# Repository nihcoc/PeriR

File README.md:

# PeriR
> Under Development!

---

## Abstract

A custom Software Defined Radio (SDR) HAT built around the Xilinx Artix-7 XC7A50T FPGA and Analog Devices AD9364 RF transceiver.
This project is inspired by the [FreeSRP](http://electronics.kitchen/misc/freesrp/) open-source SDR by Lukas Lao Beyer and design references from the  <a href="https://wiki.analog.com/resources/eval/user-guides/ad-fmcomms4-ebz">FMCOMMS4</a>.

The goal is a powerful, Linux-capable SDR transceiver with a compact form factor and eventually, a handheld device like the HackRF Portapack.

---

## Key Specifications

| Feature | Detail |
|---|---|
| **SoM** | Compute Module 4 |
| **FPGA** | Xilinx Artix-7 XC7A50T FPGA |
| **RF Transceiver** | Analog Devices AD9364 |
| **Frequency Range** | 70 MHz – 6.0 GHz |
| **Bandwidth** | 200 kHz – 56 MHz |
| **Interfaces** | PCIe 2.0 x1, USB2.0 |
---

## Hardware Design

Read my <a href="https://github.com/nihcoc/PeriR/blob/main/perir-journal.md">Hardware Journal and 120 Hours of footage of my entire design process</a> here!

### RF
- **Balun:** TCM1-63AX+ wideband RF transformer (10MHz to 6GHz)
- **Clock:** 40 MHz TCXO
- **Power:** ADP1754ACPZ-1.3-R7 (Recommended by AD)
- **TX Power Amp:** PGA-102 (dedicated clean 3.3V supply)
- **Trace:** Output traces are 50Ω controlled for the JLC06161H-3313A stack-up, Co-planar and no solder mask

### Power Architecture

| Rail | IC | Current | 
|---|---|---|
| 1.0V | TPS62130A | 3A | 
| 1.8V | TPS62130A | 3A | 
| 3.3V | TPS62130A | 3A | 
| 2.5V | TPS62130A | 3A | 
| 1.2V | TPS62130A | 3A | 
| 1.3V | ADP1754ACPZ-1.3-R7 | 3A |
| 5V | External connector | ~ 8A  |

> Sequencing is managed using EN (Enable) and PG (Power Good) pins chained between power ICs. See Pg8 on ([DS181](https://docs.amd.com/v/u/en-US/ds181_Artix_7_Data_Sheet))

### Interfaces
**CM4 INTERFACES**
| CM4 Interface | Notes |
|---|---|
| **HDMI** | Length matched, 100Ω  Differential|
| **USB** | Length matched, 100Ω  Differential|
| **DSI** | Length matched, 100Ω  Differential |
| **SD Card** |  Length matched, 50Ω |
| **PCIe 2.0 x1** | ±1ps Length matched , 90Ω Differential (See ([Pg7 2.3](https://pip-assets.raspberrypi.com/categories/634-raspberry-pi-compute-module-4/documents/RP-008168-DS-4-cm4-datasheet.pdf)) ) |
| **DEBUG LEDS** | Blue leds for debug/status |

> Impedance controlled according to the JLC06161H-3313A stack-up using the [JLCPCB impedence calculator](https://jlcpcb.com/pcb-impedance-calculator)

**FPGA INTERFACES**
| FPGA Interface | Notes |
|---|---|
| **USB 2.0** | Routed for the asynchronous 245 FIFO mode on FT2232HL |
| **PCIe 2.0 x1** | GTP transceivers are only supported on a few Artix-7 chips such as the CSG-325 |
| **JTAG** | Bank_0 |
| **Transceiver Digital Interface** | Routing configured for the DUAL PORT FULL DUPLEX MODE using the LVDS signaling standard. LVDS mode is supported on the XC7A50T-CSG325 but only when VCCO_x is supplied with 2.5V|
| **DEBUG LEDS** | Blue leds for debug/status |

> Impedance for the layer 3 LVDS signals is not 100Ω because I mistakenly used the JLC06161H-3313E stackup to calculate the impedance for this layer. It's not ideal, but the traces are only around 3 cm long, so the impact of the mismatch should be relatively small. I can validate the interface at a lower data rate and use diagnostics and timing analysis to check the signal margin. I'll fix the impedance mismatch properly in V2.

---

###  Key Datasheets

| Part | Source |
|---|---|
| **XC7A50T** | [UG470 CONFIG/FLASH](https://docs.amd.com/v/u/en-US/ug470_7Series_Config) |
| **XC7A50T** | [DS181 POWER](https://docs.amd.com/v/u/en-US/ds181_Artix_7_Data_Sheet) |
| **XC7A50T** | [UG483 LAYOUT/CAPS](https://docs.amd.com/v/u/en-US/ug483_7Series_PCB) |
| **XC7A50T** | [UG482 GTP(PCIe)](https://docs.amd.com/v/u/en-US/ug482_7Series_GTP_Transceivers) |
| **XC7A50T** | [UG472 CLOCKING ](https://docs.amd.com/v/u/en-US/ug472_7Series_Clocking) |
| **AD9364** | [UG673 Main Reference](https://www.analog.com/media/en/technical-documentation/data-sheets/AD9364.pdf) |
| **AD9364** | [Overview](https://www.scribd.com/document/271013063/AD9364-Reference-Manual-UG-673) |
| **FT2232H** | [Main Reference](https://ftdichip.com/wp-content/uploads/2024/09/DS_FT2232H.pdf) |
| **Compute Module 4** | [Main Reference](https://pip-assets.raspberrypi.com/categories/634-raspberry-pi-compute-module-4/documents/RP-008168-DS-4-cm4-datasheet.pdf)|
| **TPS62130** | [Main Reference](https://www.ti.com/lit/gpn/TPS62130A)|
| **ADP1754ACPZ-1.3-R7** | [Main Reference](https://www.analog.com/media/en/technical-documentation/data-sheets/ADP1754_1755.pdf)|
| **NCP700BSN33T1G** | [Main Reference](https://www.onsemi.com/pdf/datasheet/ncp700b-d.pdf)|
| **ADM7160AUJZ-1.8-R7** | [Main Reference](https://www.analog.com/media/en/technical-documentation/data-sheets/ADM7160.pdf)|
| **TCM1-63AX+** | [Main Reference](https://www.minicircuits.com/pdfs/TCM1-63AX+.pdf)|
| **PGA-102+** | [Main Reference](https://www.minicircuits.com/pdfs/PGA-102+.pdf)|

---

## Software

CM4 - FPGA - AD9364 software/digital design interface is in development.

**General Software**

- **OS:** [Kuiper Linux](https://wiki.analog.com/resources/tools-software/linux-software/kuiper-linux) by Analog Devices
- **Reference HDL:** ([https://github.com/analogdevicesinc/hdl/blob/main/library/axi_ad9361/axi_ad9361.v](https://github.com/analogdevicesinc/hdl/blob/main/library/axi_ad9361/axi_ad9361.v))

---

## Layers

*Layer 1(Top)*

*Layer 2(GND)*

*Layer 3*

*Layer 4(Power)*
> IDK how I didn't notice but my power planes look hideous and probably subpar with those sharp edges and uneven clearances. Gotta fix this in V2.

*Layer 5(GND/LOW Speed Signals)*

*Layer 6(Bottom)*

---

## Bill of Materials

 Total = ~$485(excl. shipping)

| # | LCSC# | MPN | Manufacturer | Package | Board Ref | Description | Qty | MOQ | Unit Price ($) | Ext. Price ($) | Product Link |
|---|-------|-----|--------------|---------|-----------|-------------|-----|-----|---------------|----------------|--------------|
| 1 | C444946 | AD9364BBCZ | ADI | BGA-144 | U4 | -122dBm 70MHz~6GHz 1.2V~3.3V BGA-144 RF Transceiver ICs RoHS | 1 | 1 | 96.5166 | 96.52 | [Link](https://www.lcsc.com/product-detail/C444946.html) |
| 2 | C5199907 | SMA-J-P-H-ST-EM1 | Samtec | SMD | J12, J13, J14 | Connector Receptacle SMA 50Ω | 3 | 1 | 4.8959 | 14.69 | [Link](https://www.lcsc.com/product-detail/C5199907.html) |
| 3 | C337502 | TPS62130ARGTR | TI | QFN-16-EP(3x3) | U7, U8, U9, U10, U12 | 2.5MHz Step-down type Adjustable 900mV~6V 3A QFN-16-EP(3x3) Voltage Regulators - DC DC Switching Regulators RoHS | 5 | 1 | 0.7910 | 3.96 | [Link](https://www.lcsc.com/product-detail/C337502.html) |
| 4 | C9002 | X322512MSB4SI | YXC Crystal Oscillators | SMD3225-4P | Y4 | Crystal 12MHz ±10ppm 20pF SMD3225-4P | 5 | 5 | 0.1012 | 0.51 | [Link](https://www.lcsc.com/product-detail/C9002.html) |
| 5 | C55061480 | PUBFA-R23A-003 | YUWENFA | Through Hole | J7 | USB 2.0 Through Hole USB, DVI, HDMI Connector Adapters RoHS | 5 | 5 | 0.0583 | 0.29 | [Link](https://www.lcsc.com/product-detail/C55061480.html) |
| 6 | C720616 | HDMI-001S | XUNPU | SMD | J5 | HDMI-A Receptacle Connector 19 Position Surface Mount, Right Angle | 5 | 5 | 0.2424 | 1.21 | [Link](https://www.lcsc.com/product-detail/C720616.html) |
| 7 | C2765186 | TYPE-C 16PIN 2MD(073) | SHOU HAN | SMD | J9 | USB-C (USB TYPE-C) Receptacle Connector 16 Position Surface Mount, Right Angle | 20 | 20 | 0.0707 | 1.41 | [Link](https://www.lcsc.com/product-detail/C2765186.html) |
| 8 | C7529389 | TF-CARD H1.8 | SHOU HAN | SMD | J2 | Micro SD card (TF card) Connector and Ejector Push-Push Surface Mount | 10 | 10 | 0.0608 | 0.61 | [Link](https://www.lcsc.com/product-detail/C7529389.html) |
| 9 | C720557 | DC-005-A200 | XUNPU | Through Hole | J10 | Power Barrel Connector Jack 2mm ID 6.4mm OD Through Hole, Right Angle | 5 | 5 | 0.1294 | 0.65 | [Link](https://www.lcsc.com/product-detail/C720557.html) |
| 10 | C502010 | MLJ1608WR33JT000 | TDK | 0603 | L13, L14 | 500mA 330nH ±5% 320mΩ 650mA Multilayer inductor 0603 Fixed Inductors RoHS | 10 | 10 | 0.0744 | 0.74 | [Link](https://www.lcsc.com/product-detail/C502010.html) |
| 11 | C85837 | BLM21AG601SN1D | muRata | 0805 | FB4 | 600Ω@100MHz 1 Line Ferrite Bead 0805 700mA 210mΩ | 20 | 20 | 0.0618 | 1.24 | [Link](https://www.lcsc.com/product-detail/C85837.html) |
| 12 | C424649 | DF40HC(3.0)-100DS-0.4V(51) | HRS | SMD, P=0.4mm | H1 | High-Density Board-to-Board Connector 100-pos 0.4mm pitch | 2 | 1 | 1.8918 | 3.78 | [Link](https://www.lcsc.com/product-detail/C424649.html) |
| 13 | C25120 | 0402WGF499JTCE | UNI-ROYAL | 0402 | R33 | 49.9Ω ±1% 62.5mW 0402 Thick Film Resistor | 100 | 100 | 0.0011 | 0.11 | [Link](https://www.lcsc.com/product-detail/C25120.html) |
| 14 | C2906901 | FRC0402J1R0 TS | FOJAN | 0402 | R31, R32 | 1Ω ±5% 62.5mW 0402 Thick Film Resistor | 100 | 100 | 0.0016 | 0.16 | [Link](https://www.lcsc.com/product-detail/C2906901.html) |
| 15 | C852856 | RT0402BRD075K1L | YAGEO | 0402 | R27, R28 | 5.1kΩ 62.5mW 50V Thin Film Resistor ±25ppm/℃ ±0.1% 0402 Chip Resistor - Surface Mount RoHS | 50 | 50 | 0.0216 | 1.08 | [Link](https://www.lcsc.com/product-detail/C852856.html) |
| 16 | C2909316 | FRC0402F1202TS | FOJAN | 0402 | R25 | 12kΩ ±1% 62.5mW 0402 Thick Film Resistor | 100 | 100 | 0.0014 | 0.14 | [Link](https://www.lcsc.com/product-detail/C2909316.html) |
| 17 | C190095 | RT0402BRD0710KL | YAGEO | 0402 | R19, R20, R24, R30, R35 | 62.5mW 10kΩ 50V Thin Film Resistor ±25ppm/℃ ±0.1% 0402 Chip Resistor - Surface Mount RoHS | 50 | 50 | 0.0207 | 1.04 | [Link](https://www.lcsc.com/product-detail/C190095.html) |
| 18 | C2906865 | FRC0402F2201TS | FOJAN | 0402 | R17, R18 | 2.2kΩ ±1% 62.5mW 0402 Thick Film Resistor | 100 | 100 | 0.0016 | 0.16 | [Link](https://www.lcsc.com/product-detail/C2906865.html) |
| 19 | C106232 | RC0402FR-07100RL | YAGEO | 0402 | R8 | 100Ω 62.5mW 50V Thick Film Resistor ±100ppm/℃ ±1% 0402 Chip Resistor - Surface Mount RoHS | 100 | 100 | 0.0013 | 0.13 | [Link](https://www.lcsc.com/product-detail/C106232.html) |
| 20 | C242160 | ERJ2GE0R00X | PANASONIC | 0402 | R7 | 100mW 0Ω Thick Film Resistor -100ppm/℃~+600ppm/℃ 0402 Chip Resistor - Surface Mount RoHS | 100 | 100 | 0.0047 | 0.47 | [Link](https://www.lcsc.com/product-detail/C242160.html) |
| 21 | C71626 | CRCW0402330RFKED | VISHAY | 0402 | R5 | 63mW 330Ω Thick Film Resistor ±100ppm/℃ ±1% 0402 Chip Resistor - Surface Mount RoHS | 100 | 100 | 0.0037 | 0.37 | [Link](https://www.lcsc.com/product-detail/C71626.html) |
| 22 | C1884625 | MCS04020C4701FE000 | VISHAY | 0402 | R2, R3, R29 | 100mW 4.7kΩ 50V Thin Film Resistor ±50ppm/℃ ±1% 0402 Chip Resistor - Surface Mount RoHS | 20 | 20 | 0.0304 | 0.61 | [Link](https://www.lcsc.com/product-detail/C1884625.html) |
| 23 | C852624 | RT0402BRD071KL | YAGEO | 0402 | R1, R2(DNP), R3(DNP), R4, R5(DNP), R6, R26 | 1kΩ 62.5mW 50V Thin Film Resistor ±25ppm/℃ ±0.1% 0402 Chip Resistor - Surface Mount RoHS | 50 | 50 | 0.0199 | 1.00 | [Link](https://www.lcsc.com/product-detail/C852624.html) |
| 24 | C5633358 | ECS-TXO-32CSMV-400-BN-TR | ECS | SMD3225-4P | Y6 | 40MHz SMD3225-4P Oscillators RoHS | 1 | 1 | 2.6285 | 2.63 | [Link](https://www.lcsc.com/product-detail/C5633358.html) |
| 25 | C7522691 | LQW18AS43NJ00D | muRata | 0603 | L11 | 600mA 43nH ±5% 280mΩ Wire-wound chip inductor 0603 Fixed Inductors RoHS | 5 | 5 | 0.0895 | 0.45 | [Link](https://www.lcsc.com/product-detail/C7522691.html) |
| 26 | C51048295 | FRC0402F1432TS | FOJAN | 0402 | R34 | 62.5mW 14.3kΩ 50V Thick Film Resistor ±1% 0402 Chip Resistor - Surface Mount RoHS | 100 | 100 | 0.0008 | 0.08 | [Link](https://www.lcsc.com/product-detail/C51048295.html) |
| 27 | C2906952 | FRC0402J513 TS | FOJAN | 0402 | R84 | 51kΩ ±5% 62.5mW 0402 Thick Film Resistor | 100 | 100 | 0.0013 | 0.13 | [Link](https://www.lcsc.com/product-detail/C2906952.html) |
| 28 | C144785 | AC0402FR-07200KL | YAGEO | 0402 | R85, R125 | 62.5mW 200kΩ 50V Thick Film Resistor ±100ppm/℃ ±1% 0402 Chip Resistor - Surface Mount RoHS | 100 | 100 | 0.0018 | 0.18 | [Link](https://www.lcsc.com/product-detail/C144785.html) |
| 29 | C481918 | CRCW0402100KFKED | VISHAY | 0402 | R86, R87, R88, R89, R91, R127, R129, R133 | 100kΩ 63mW 50V Thick Film Resistor ±1% ±100ppm/℃ 0402 Chip Resistor - Surface Mount RoHS | 100 | 100 | 0.0038 | 0.38 | [Link](https://www.lcsc.com/product-detail/C481918.html) |
| 30 | C7467320 | FRC0402J164 TS | FOJAN | 0402 | R126 | 62.5mW 160kΩ 50V Thick Film Resistor ±5% ±100ppm/℃ 0402 Chip Resistor - Surface Mount RoHS | 100 | 100 | 0.0011 | 0.11 | [Link](https://www.lcsc.com/product-detail/C7467320.html) |
| 31 | C2906873 | FRC0402F4992TS | FOJAN | 0402 | R128 | 49.9kΩ ±1% 62.5mW 0402 Thick Film Resistor | 100 | 100 | 0.0015 | 0.15 | [Link](https://www.lcsc.com/product-detail/C2906873.html) |
| 32 | C2515044 | RN73H1ETTP2133D25 | KOA | 0402 | R130 | 62.5mW 213kΩ Metal Film Resistor ±0.5% ±25ppm/℃ 0402 Chip Resistor - Surface Mount RoHS | 1 | 1 | 0.0568 | 0.06 | [Link](https://www.lcsc.com/product-detail/C2515044.html) |
| 33 | C4180598 | RE0402BRE07309KL | YAGEO | 0402 | R134 | 309kΩ 62.5mW Thick Film Resistor ±50ppm/℃ ±0.1% 0402 Chip Resistor - Surface Mount RoHS | 20 | 20 | 0.0111 | 0.22 | [Link](https://www.lcsc.com/product-detail/C4180598.html) |
| 34 | C494678 | TCM1-63AX+ | Mini-Circuits | SMD-6P | T4, T6 | 9.42dB 8° 10MHz~6GHz 2.5dB 50Ω:50Ω SMD-6P Balun RoHS | 2 | 1 | 17.6099 | 35.22 | [Link](https://www.lcsc.com/product-detail/C494678.html) |
| 35 | C1521759 | XC7A50T-2CSG325I | AMD/XILINX | FPGA-325(15x15) | U2 | 52160 FPGA-325(15x15) FPGAs (Field Programmable Gate Array) RoHS | 1 | 1 | 52.4575 | 52.46 | [Link](https://www.lcsc.com/product-detail/C1521759.html) |
| 36 | C27882 | FT2232HL-REEL | FTDI | LQFP-64(10x10) | U3 | 480Mbps USB 2.0 LQFP-64(10x10) Interface Controllers RoHS | 1 | 1 | 12.4162 | 12.42 | [Link](https://www.lcsc.com/product-detail/C27882.html) |
| 37 | C3193264 | PGA-102+ | Mini-Circuits | SOT-89 | U11 | 10.4dB 50MHz~6GHz 3.1V~3.5V 3.9dB 17.5dBm 83mA SOT-89 RF Amplifiers RoHS | 1 | 1 | 2.3356 | 2.34 | [Link](https://www.lcsc.com/product-detail/C3193264.html) |
| 38 | C1997058 | SG-8018CA 100.0000M-TJHSA0 | EPSON | SMD7050-4P | Y2 | 100MHz SMD7050-4P Oscillators RoHS | 1 | 1 | 1.0742 | 1.07 | [Link](https://www.lcsc.com/product-detail/C1997058.html) |
| 39 | C76941 | GRM033R71A103KA01D | muRata | 0201 | C284, C292, C305 | 10nF ±10% 10V Ceramic Capacitor X7R 0201 | 100 | 100 | 0.0050 | 0.50 | [Link](https://www.lcsc.com/product-detail/C76941.html) |
| 40 | C368809 | CL05A475KP5NRNC | Samsung Electro-Mechanics | 0402 | C1, C2, C9, C12, C13, C18, C19, C24, C25, C30, C31, C46, C85, C86, C313 | 4.7uF ±10% 10V Ceramic Capacitor X5R 0402 | 50 | 50 | 0.0116 | 0.58 | [Link](https://www.lcsc.com/product-detail/C368809.html) |
| 41 | C6663208 | 298W107X0004M2T | VISHAY | 0603 | C3, C14 | 100uF ±20% 4V Tantalum Capacitors 0603 | 2 | 1 | 1.8719 | 3.74 | [Link](https://www.lcsc.com/product-detail/C6663208.html) |
| 42 | C92361 | CL05A474KA5NNNC | Samsung Electro-Mechanics | 0402 | C4, C5, C6, C11, C15, C16, C17, C20, C21, C22, C23, C26, C27, C28, C29, C32, C33, C34, C35 | 470nF ±10% 25V Ceramic Capacitor X5R 0402 | 20 | 10 | 0.0163 | 0.33 | [Link](https://www.lcsc.com/product-detail/C92361.html) |
| 43 | C60474 | CC0402KRX7R7BB104 | YAGEO | 0402 | C267, C271, C277, C287, C289, C291, C295, C296, C310, C320 | 100nF ±10% 16V Ceramic Capacitor X7R 0402 | 200 | 100 | 0.0072 | 1.44 | [Link](https://www.lcsc.com/product-detail/C60474.html) |
| 44 | C140782 | GRM188R60J476ME15D | muRata | 0603 | C10, C42, C43, C265, C269, C274, C281, C285, C288, C290, C293, C308 | 47uF ±20% 6.3V Ceramic Capacitor X5R 0603 | 20 | 10 | 0.1431 | 2.86 | [Link](https://www.lcsc.com/product-detail/C140782.html) |
| 45 | C51412 | CL10A335KP8NNNC | Samsung Electro-Mechanics | 0603 | C77 | 3.3uF ±10% 10V Ceramic Capacitor X5R 0603 | 10 | 10 | 0.0311 | 0.31 | [Link](https://www.lcsc.com/product-detail/C51412.html) |
| 46 | C384976 | GRM0335C1H270GA01D | muRata | 0201 | C89, C90 | 27pF ±2% 50V Ceramic Capacitor C0G 0201 | 100 | 100 | 0.0048 | 0.48 | [Link](https://www.lcsc.com/product-detail/C384976.html) |
| 47 | C29266 | CL05A105KO5NNNC | Samsung Electro-Mechanics | 0402 | C91, C97, C304, C306, C307, C314 | 1uF ±10% 16V Ceramic Capacitor X5R 0402 | 100 | 100 | 0.0072 | 0.72 | [Link](https://www.lcsc.com/product-detail/C29266.html) |
| 48 | C307380 | CL03A104KO3NNNC | Samsung Electro-Mechanics | 0201 | C99, C100, C101, C102, C103, C105, C106, C107, C108, C109, C111, C112, C113, C115, C117, C118, C119, C312 | 100nF ±10% 16V Ceramic Capacitor X5R 0201 | 200 | 100 | 0.0029 | 0.58 | [Link](https://www.lcsc.com/product-detail/C307380.html) |
| 49 | C19702 | CL10A106KP8NNNC | Samsung Electro-Mechanics | 0603 | C104, C110, C114, C116, C266, C270, C275, C283, C286, C294, C309, C321 | 10uF ±10% 10V Ceramic Capacitor X5R 0603 | 20 | 20 | 0.0822 | 1.64 | [Link](https://www.lcsc.com/product-detail/C19702.html) |
| 50 | C62164 | 0201CG180J500NT | FH | 0201 | C120, C121, C317, C318 | 18pF ±5% 50V Ceramic Capacitor C0G 0201 | 100 | 100 | 0.0029 | 0.29 | [Link](https://www.lcsc.com/product-detail/C62164.html) |
| 51 | C161488 | GRM033R71E222KA12D | muRata | 0201 | C262, C264, C272, C280, C303 | 2.2nF ±10% 25V Ceramic Capacitor X7R 0201 | 100 | 100 | 0.0052 | 0.52 | [Link](https://www.lcsc.com/product-detail/C161488.html) |
| 52 | C86295 | CL10A226MP8NUNE | Samsung Electro-Mechanics | 0603 | C263, C268, C278, C297 | 22uF ±20% 10V Ceramic Capacitor X5R 0603 | 10 | 10 | 0.0380 | 0.38 | [Link](https://www.lcsc.com/product-detail/C86295.html) |
| 53 | C122469 | XFL4020-222MEC | Coilcraft | SMD, 4x4mm | L7, L8, L9, L10, L12 | 8A 2.2uH ±20% 21.35mΩ 3.7A SMD 4x4mm Fixed Inductors RoHS | 5 | 1 | 1.3566 | 6.78 | [Link](https://www.lcsc.com/product-detail/C122469.html) |
| 54 | C602037 | CL21A226MAYNNNE | Samsung Electro-Mechanics | 0805 | C311 | 22uF ±20% 25V Ceramic Capacitor X5R 0805 | 10 | 10 | 0.1135 | 1.14 | [Link](https://www.lcsc.com/product-detail/C602037.html) |
| 55 | C17291088 | GCM033R71A122KA03D | muRata | 0201 | C315 | 1.2nF X7R ±10% 10V 0201 Ceramic Capacitors RoHS | 100 | 100 | 0.0094 | 0.94 | [Link](https://www.lcsc.com/product-detail/C17291088.html) |
| 56 | C88914 | GRM0335C1H680JA01D | muRata | 0201 | C316 | 68pF ±5% 50V Ceramic Capacitor C0G 0201 | 100 | 100 | 0.0017 | 0.17 | [Link](https://www.lcsc.com/product-detail/C88914.html) |
| 57 | C505464 | CC0201KRX7R9BB102 | YAGEO | 0201 | C319 | 1nF ±10% 50V Ceramic Capacitor X7R 0201 | 100 | 100 | 0.0018 | 0.18 | [Link](https://www.lcsc.com/product-detail/C505464.html) |
| 58 | C133346 | ESD8472MUT5G | onsemi | X3-DFN-2(0.3x0.6) | D5, D12 | 15V Clamp 20V Clamp 3A@8/20us Ipp ESD DIODE X3-DFN-2(0.3x0.6) | 5 | 5 | 0.0826 | 0.41 | [Link](https://www.lcsc.com/product-detail/C133346.html) |
| 59 | C598848 | MT25QU128ABA8ESF-0SIT | Micron | SOIC-16-300mil | IC1 | SOIC-16-300mil NOR Flash Memory RoHS | 1 | 1 | 10.2374 | 10.24 | [Link](https://www.lcsc.com/product-detail/C598848.html) |
| 60 | C613841 | 93C46B/P | MICROCHIP | PDIP-8 | IC3 | 1Kbit 4.5V~5.5V 2MHz SPI PDIP-8 Memory (ICs) RoHS | 1 | 1 | 1.0827 | 1.08 | [Link](https://www.lcsc.com/product-detail/C613841.html) |
| 61 | C3747719 | ADP1754ACPZ-1.3-R7 | ADI | LFCSP-16(4x4) | IC10, IC11 | 1.3V Positive Fixed LFCSP-16(4x4) Voltage Regulators - Linear, Low Drop Out (LDO) Regulators RoHS | 2 | 1 | 4.6333 | 9.27 | [Link](https://www.lcsc.com/product-detail/C3747719.html) |
| 62 | C892685 | NCP700BSN33T1G | onsemi | TSOP-5-1.5mm | IC13 | 3.3V Positive Fixed TSOP-5-1.5mm Voltage Regulators - Linear, Low Drop Out (LDO) Regulators RoHS | 1 | 1 | 1.2691 | 1.27 | [Link](https://www.lcsc.com/product-detail/C892685.html) |
| 63 | C658468 | ADM7160AUJZ-1.8-R7 | ADI | TSOT-5 | IC14 | Linear Voltage Regulator IC Positive Fixed 1 Output 200mA TSOT-5 | 1 | 1 | 2.7671 | 2.77 | [Link](https://www.lcsc.com/product-detail/C658468.html) |
| 64 | C5410688 | 69145-210LF | Amphenol | — | J1 | Open-Top 2.54mm Shunts, Jumpers RoHS | 1 | 1 | 1.0308 | 1.03 | [Link](https://www.lcsc.com/product-detail/C5410688.html) |
| 65 | C3168185 | FH19SC-22S-0.5SH(09) | HRS | SMD, P=0.5mm | J6 | FFC/FPC Connector 22 Position 0.5mm Pitch Bottom Contact Surface Mount, Right Angle | 1 | 1 | 1.7125 | 1.71 | [Link](https://www.lcsc.com/product-detail/C3168185.html) |
| 66 | --- | Compute Module 4 CM4101000 WIFI Lite | RPi | --- | --- | --- | 1 | 1 | 95 | 95 | [Link](https://ar.aliexpress.com/item/1005008557413104.html?spm=a2g0o.productlist.main.2.4574vHeWvHeWo5&algo_pvid=dbca0ea5-76ce-4cef-a374-f51fa96f5d17&algo_exp_id=dbca0ea5-76ce-4cef-a374-f51fa96f5d17-1&pdp_ext_f=%7B%22order%22%3A%2256%22%2C%22eval%22%3A%221%22%2C%22fromPage%22%3A%22search%22%7D&pdp_npi=6%40dis%21AED%21291.96%21291.96%21%21%21522.94%21522.94%21%40214100f417822410718697426e529a%2112000045700124987%21sea%21AE%210%21ABX%211%210%21n_tag%3A-29910%3Bd%3Ae64a854d%3Bm03_new_user%3A-29895&curPageLogUid=OTnqg2gbWbCW&utparam-url=scene%3Asearch%7Cquery_from%3A%7Cx_object_id%3A1005008557413104%7C_p_origin_prod%3A) |
| 67 | --- | PCBA | JLCPCB | --- | --- | 6 - Layer | 1 | 1 | 100 | 100 | --- |

---
*Special Thanks to Hack Club and the fabulous people at Fallout 2026!*

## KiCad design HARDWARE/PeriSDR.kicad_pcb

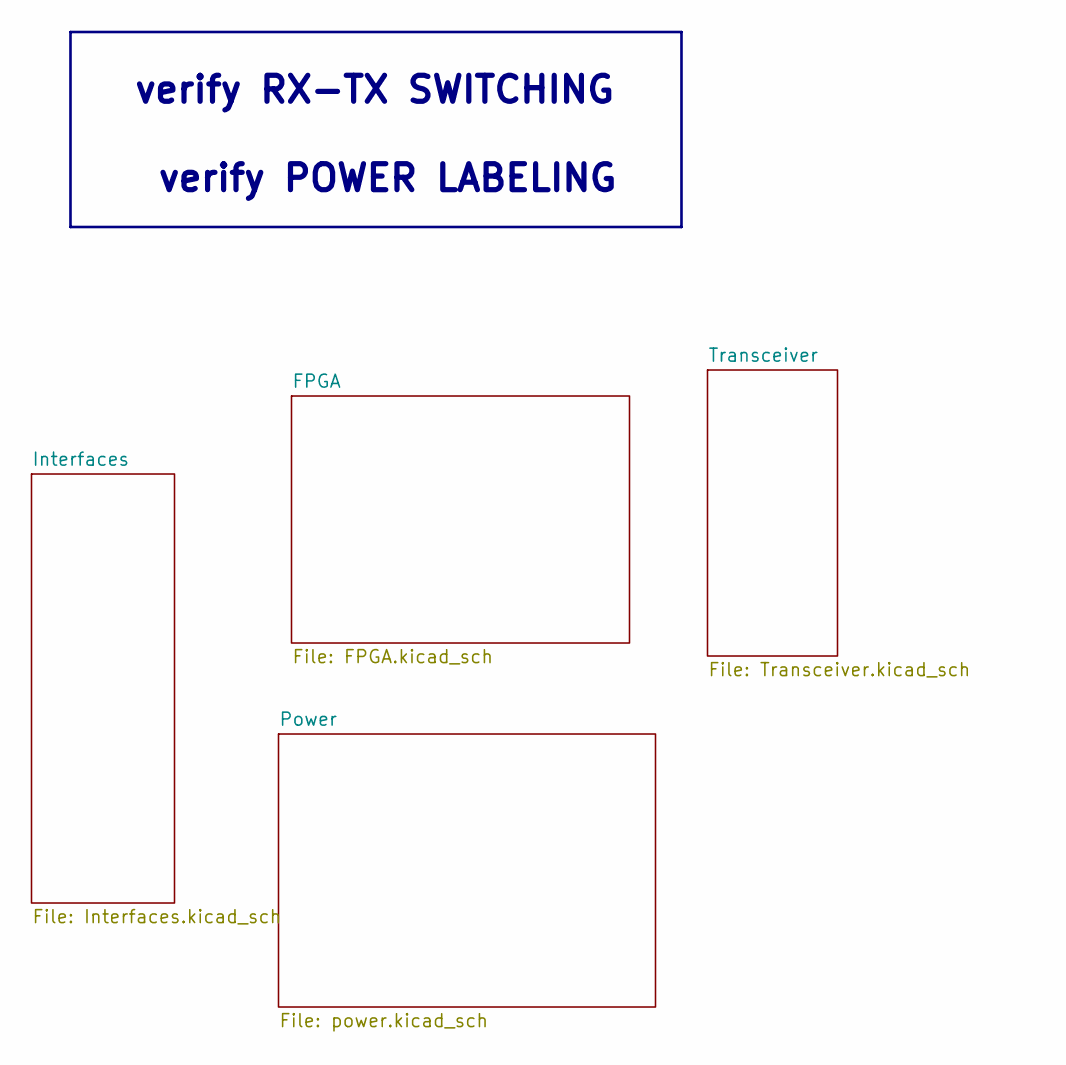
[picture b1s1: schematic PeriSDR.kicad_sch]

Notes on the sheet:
verify RX-TX SWITCHING
verify POWER LABELING

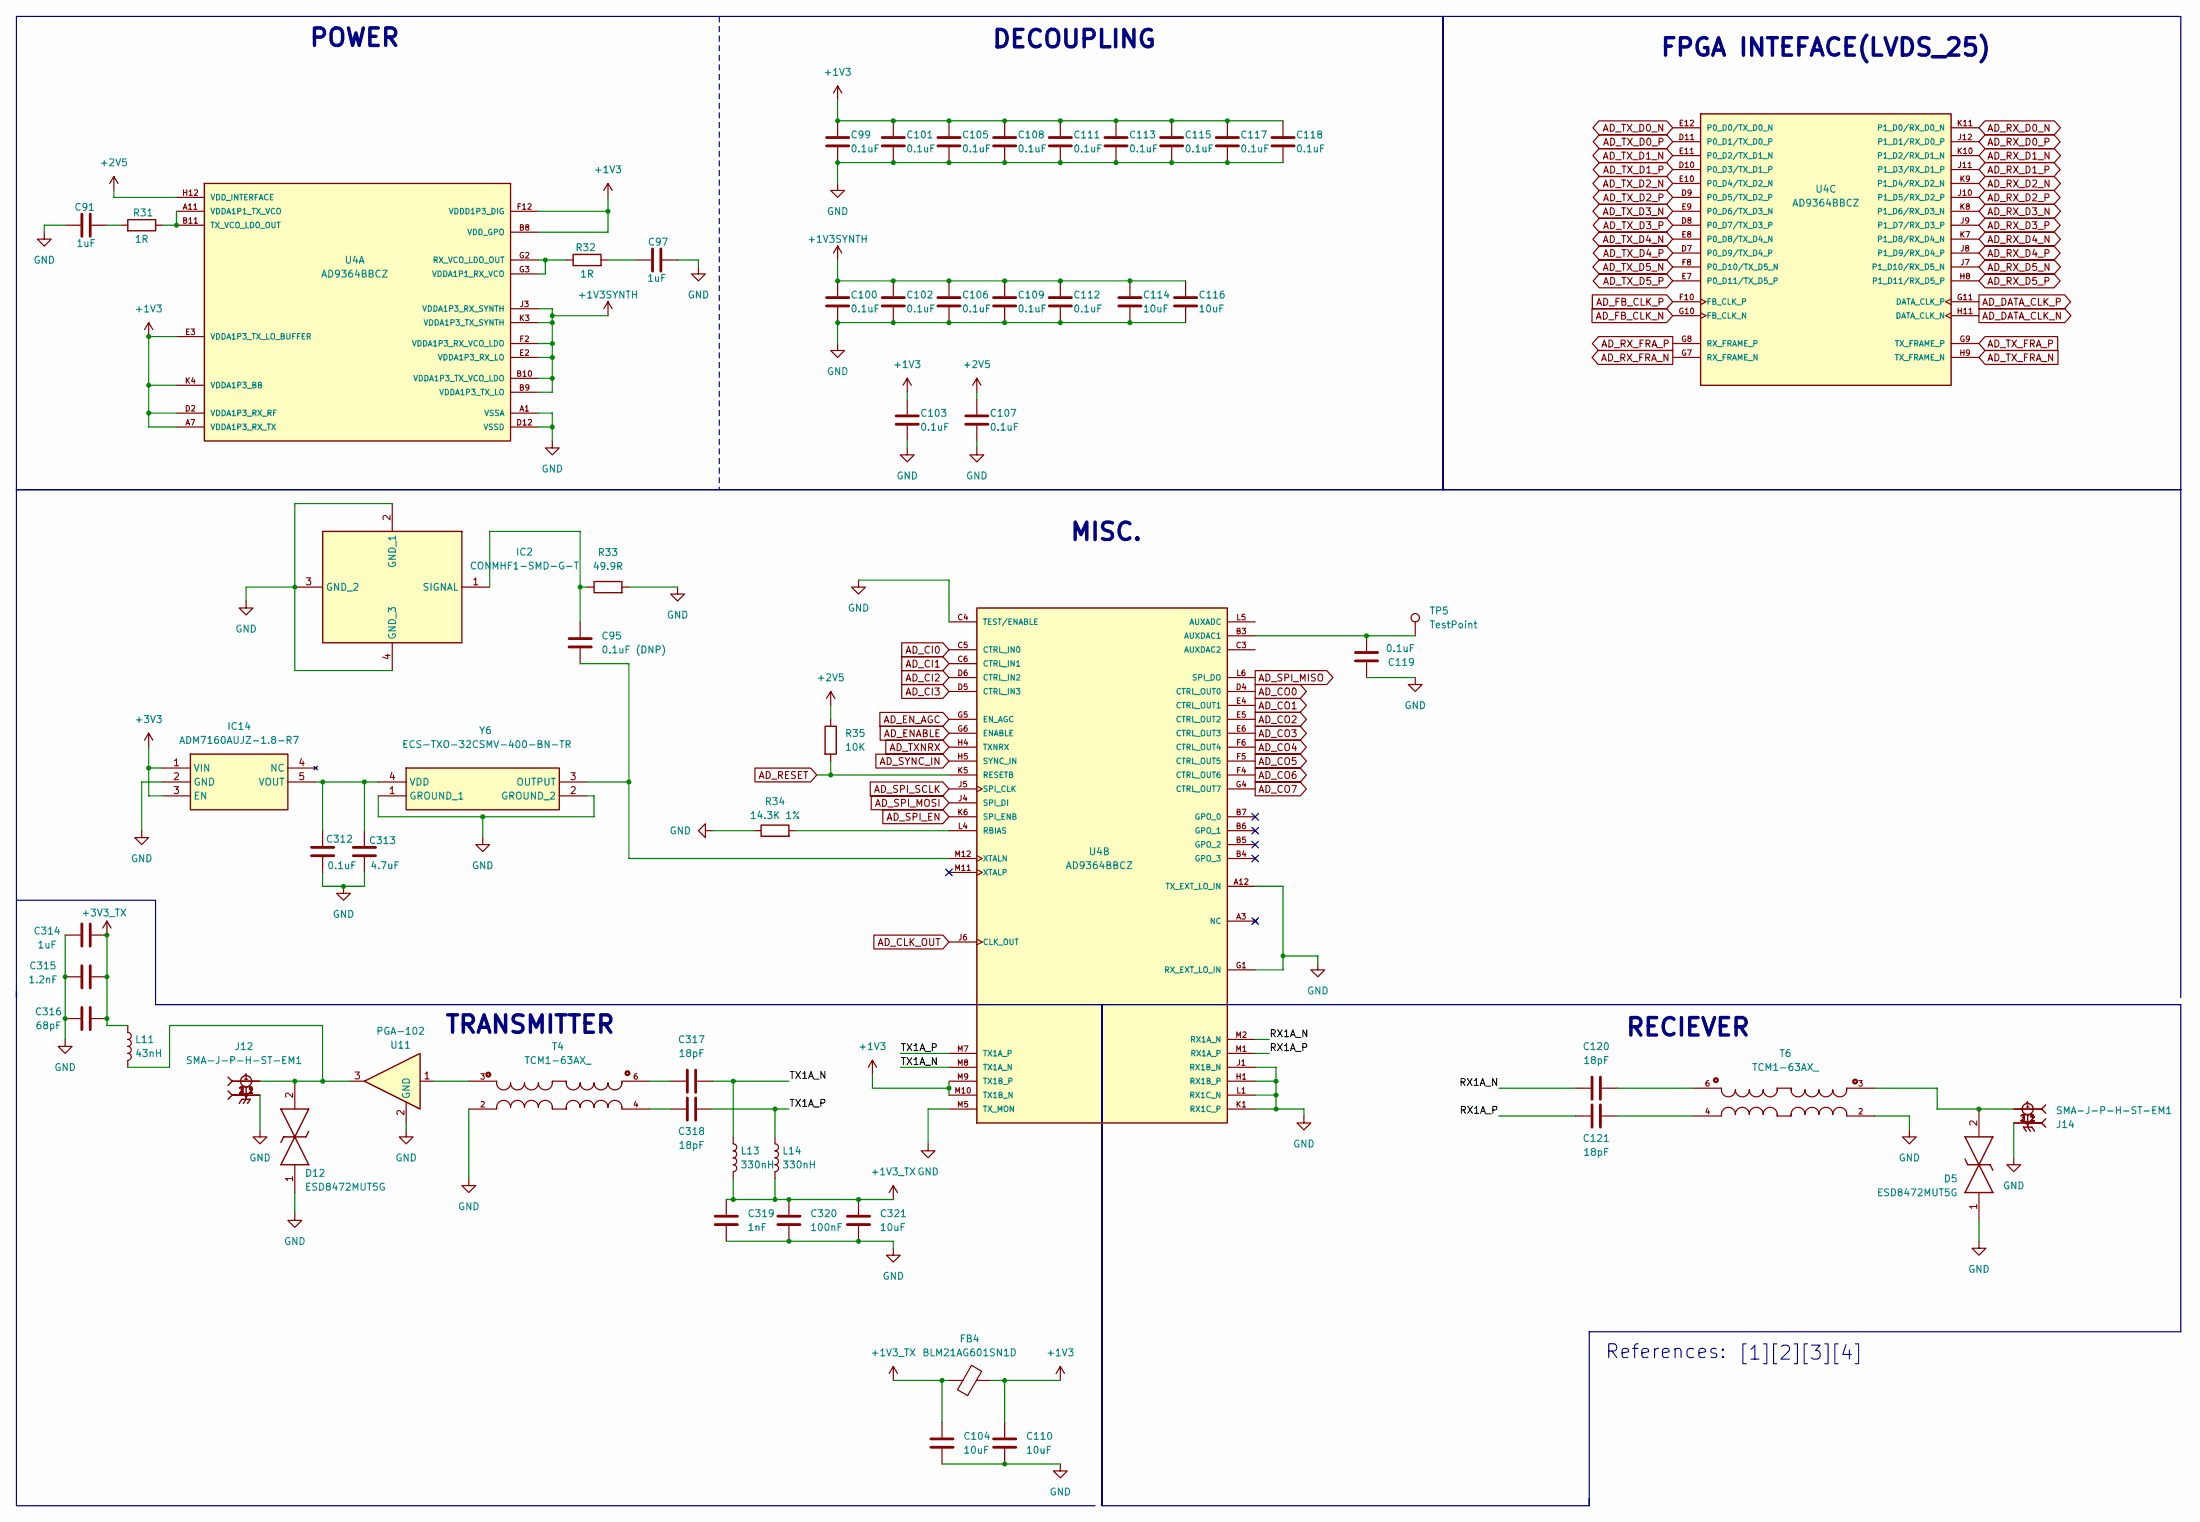
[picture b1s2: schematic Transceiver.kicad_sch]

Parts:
C91, C97, C314: 1uF; C_0402_1005Metric
C95: 0.1uF (DNP); C_0201_0603Metric
C99, C100, C101, C102, C103, C105, C106, C107, C108, C109, C111, C112, C113, C115, C117, C118, C119, C312: 0.1uF; C_0201_0603Metric
C104, C110, C114, C116, C321: 10uF; C_0603_1608Metric
C120, C121, C317, C318: 18pF; C_0201_0603Metric
C313: 4.7uF; C_0402_1005Metric
C315: 1.2nF; C_0201_0603Metric
C316: 68pF; C_0201_0603Metric
C319: 1nF; C_0201_0603Metric
C320: 100nF; C_0402_1005Metric
D5, D12: ESD8472MUT5G; X3DFN2-CASE152AF-ISSUE-A; Mouser Part Number 863-ESD8472MUT5G
FB4: BLM21AG601SN1D; L_0603_1608Metric
IC2: CONMHF1-SMD-G-T; CONMHF1SMDGT; Manufacturer_Part_Number CONMHF1-SMD-G-T
IC14: ADM7160AUJZ-1.8-R7; SOT95P280X100-5N; Manufacturer_Part_Number ADM7160AUJZ-1.8-R7; Mouser Part Number 584-ADM7160AUJZ1.8R7
J12, J14: SMA-J-P-H-ST-EM1; SAMTEC_SMA-J-P-H-ST-EM1; PARTREV G
L11: 43nH; L_0603_1608Metric
L13, L14: 330nH; L_0603_1608Metric
R31, R32: 1R; R_0402_1005Metric
R33: 49.9R; R_0402_1005Metric
R34: 14.3K 1%; R_0402_1005Metric
R35: 10K; R_0402_1005Metric
T4, T6: TCM1-63AX_; TCM163AX
TP5: TestPoint; TestPoint_Pad_1.0x1.0mm
U4: AD9364BBCZ; BGA144C80P12X12_1000X1000X170N; PARTREV C
U11: PGA-102; SOT-89-3
Y6: ECS-TXO-32CSMV-400-BN-TR; ECSTXO32CSMV400BNTR; Manufacturer_Part_Number ECS-TXO-32CSMV-400-BN-TR; Mouser Part Number 520-TXO32CSMV400BNTR

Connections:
+1V3: C99.1, C101.1, C103.1, C105.1, C108.1, C110.1, C111.1, C113.1, C115.1, C117.1, C118.1, FB4.2, U4.A7 (VDDA1P3_RX_TX), U4.A8 (VDDA1P3_RX_TX), U4.A9 (VDDA1P3_RX_TX), U4.A10 (VDDA1P3_RX_TX), U4.B8 (VDD_GPO), U4.D2 (VDDA1P3_RX_RF), U4.D3 (VDDA1P3_RX_TX), U4.E3 (VDDA1P3_TX_LO_BUFFER), U4.F12 (VDDD1P3_DIG), U4.K4 (VDDA1P3_BB), U4.M9 (TX1B_P), U4.M10 (TX1B_N); also elsewhere on the board
+1V3SYNTH: C100.1, C102.1, C106.1, C109.1, C112.1, C114.1, C116.1, U4.B9 (VDDA1P3_TX_LO), U4.B10 (VDDA1P3_TX_VCO_LDO), U4.E2 (VDDA1P3_RX_LO), U4.F2 (VDDA1P3_RX_VCO_LDO), U4.J3 (VDDA1P3_RX_SYNTH), U4.K3 (VDDA1P3_TX_SYNTH); also elsewhere on the board
+1V3_TX: C104.1, C319.1, C320.1, C321.1, FB4.1, L13.2, L14.2
+2V5: C107.1, R35.1, U4.H12 (VDD_INTERFACE); also elsewhere on the board
+3V3: IC14.1 (VIN), IC14.3 (EN); also elsewhere on the board
+3V3_TX: C314.1, C315.1, C316.1, L11.1; also elsewhere on the board
/Transceiver/RX1A_N: C120.1, U4.M2 (RX1A_N)
/Transceiver/RX1A_P: C121.1, U4.M1 (RX1A_P)
/Transceiver/TX1A_N: C317.1, L13.1, U4.M8 (TX1A_N)
/Transceiver/TX1A_P: C318.1, L14.1, U4.M7 (TX1A_P)
AD_CI0: U4.C5 (CTRL_IN0)
AD_CI1: U4.C6 (CTRL_IN1)
AD_CI2: U4.D6 (CTRL_IN2)
AD_CI3: U4.D5 (CTRL_IN3)
AD_CLK_OUT: U4.J6 (CLK_OUT); also elsewhere on the board
AD_CO0: U4.D4 (CTRL_OUT0)
AD_CO1: U4.E4 (CTRL_OUT1)
AD_CO2: U4.E5 (CTRL_OUT2)
AD_CO3: U4.E6 (CTRL_OUT3)
AD_CO4: U4.F6 (CTRL_OUT4)
AD_CO5: U4.F5 (CTRL_OUT5)
AD_CO6: U4.F4 (CTRL_OUT6)
AD_CO7: U4.G4 (CTRL_OUT7)
AD_DATA_CLK_N: U4.H11 (DATA_CLK_N); also elsewhere on the board
AD_DATA_CLK_P: U4.G11 (DATA_CLK_P); also elsewhere on the board
AD_ENABLE: U4.G6 (ENABLE); also elsewhere on the board
AD_EN_AGC: U4.G5 (EN_AGC); also elsewhere on the board
AD_FB_CLK_N: U4.G10 (FB_CLK_N); also elsewhere on the board
AD_FB_CLK_P: U4.F10 (FB_CLK_P); also elsewhere on the board
AD_RESET: R35.2, U4.K5 (RESETB); also elsewhere on the board
AD_RX_D0_N: U4.K11 (P1_D0/RX_D0_N); also elsewhere on the board
AD_RX_D0_P: U4.J12 (P1_D1/RX_D0_P); also elsewhere on the board
AD_RX_D1_N: U4.K10 (P1_D2/RX_D1_N); also elsewhere on the board
AD_RX_D1_P: U4.J11 (P1_D3/RX_D1_P); also elsewhere on the board
AD_RX_D2_N: U4.K9 (P1_D4/RX_D2_N); also elsewhere on the board
AD_RX_D2_P: U4.J10 (P1_D5/RX_D2_P); also elsewhere on the board
AD_RX_D3_N: U4.K8 (P1_D6/RX_D3_N); also elsewhere on the board
AD_RX_D3_P: U4.J9 (P1_D7/RX_D3_P); also elsewhere on the board
AD_RX_D4_N: U4.K7 (P1_D8/RX_D4_N); also elsewhere on the board
AD_RX_D4_P: U4.J8 (P1_D9/RX_D4_P); also elsewhere on the board
AD_RX_D5_N: U4.J7 (P1_D10/RX_D5_N); also elsewhere on the board
AD_RX_D5_P: U4.H8 (P1_D11/RX_D5_P); also elsewhere on the board
AD_RX_FRA_N: U4.G7 (RX_FRAME_N); also elsewhere on the board
AD_RX_FRA_P: U4.G8 (RX_FRAME_P); also elsewhere on the board
AD_SPI_EN: U4.K6 (SPI_ENB); also elsewhere on the board
AD_SPI_MISO: U4.L6 (SPI_DO); also elsewhere on the board
AD_SPI_MOSI: U4.J4 (SPI_DI); also elsewhere on the board
AD_SPI_SCLK: U4.J5 (SPI_CLK); also elsewhere on the board
AD_SYNC_IN: U4.H5 (SYNC_IN); also elsewhere on the board
AD_TXNRX: U4.H4 (TXNRX); also elsewhere on the board
AD_TX_D0_N: U4.E12 (P0_D0/TX_D0_N); also elsewhere on the board
AD_TX_D0_P: U4.D11 (P0_D1/TX_D0_P); also elsewhere on the board
AD_TX_D1_N: U4.E11 (P0_D2/TX_D1_N); also elsewhere on the board
AD_TX_D1_P: U4.D10 (P0_D3/TX_D1_P); also elsewhere on the board
AD_TX_D2_N: U4.E10 (P0_D4/TX_D2_N); also elsewhere on the board
AD_TX_D2_P: U4.D9 (P0_D5/TX_D2_P); also elsewhere on the board
AD_TX_D3_N: U4.E9 (P0_D6/TX_D3_N); also elsewhere on the board
AD_TX_D3_P: U4.D8 (P0_D7/TX_D3_P); also elsewhere on the board
AD_TX_D4_N: U4.E8 (P0_D8/TX_D4_N); also elsewhere on the board
AD_TX_D4_P: U4.D7 (P0_D9/TX_D4_P); also elsewhere on the board
AD_TX_D5_N: U4.F8 (P0_D10/TX_D5_N); also elsewhere on the board
AD_TX_D5_P: U4.E7 (P0_D11/TX_D5_P); also elsewhere on the board
AD_TX_FRA_N: U4.H9 (TX_FRAME_N); also elsewhere on the board
AD_TX_FRA_P: U4.G9 (TX_FRAME_P); also elsewhere on the board
GND: C91.2, C97.2, C99.2, C100.2, C101.2, C102.2, C103.2, C104.2, C105.2, C106.2, C107.2, C108.2, C109.2, C110.2, C111.2, C112.2, C113.2, C114.2, C115.2, C116.2, C117.2, C118.2, C119.1, C312.2, C313.2, C314.2, C315.2, C316.2, C319.2, C320.2, C321.2, D5.1, D12.1, IC2.2 (GND_1), IC2.3 (GND_2), IC2.4 (GND_3), IC14.2 (GND), J12.2_1, J12.2_2, J12.3_1, J12.3_2, J14.2_1, J14.2_2, J14.3_1, J14.3_2, R33.2, R34.1, T4.2, T6.2, U4.A1 (VSSA), U4.A2 (VSSA), U4.A4 (VSSA), U4.A5 (VSSA), U4.A6 (VSSA), U4.A12 (TX_EXT_LO_IN), U4.B1 (VSSA), U4.B2 (VSSA), U4.B12 (VSSA), U4.C1 (VSSA), U4.C2 (VSSA), U4.C4 (TEST/ENABLE), U4.C7 (VSSA), U4.C8 (VSSA), U4.C9 (VSSA), U4.C10 (VSSA), U4.C11 (VSSA), U4.C12 (VSSA), U4.D1 (VSSA), U4.D12 (VSSD), U4.E1 (VSSA), U4.F1 (VSSA), U4.F3 (VSSA), U4.F7 (VSSD), U4.F9 (VSSD), U4.F11 (VSSD), U4.G1 (RX_EXT_LO_IN), U4.G12 (VSSD), U4.H1 (RX1B_P), U4.H2 (VSSA), U4.H3 (VSSA), U4.H6 (VSSA), U4.H7 (VSSD), U4.H10 (VSSD), U4.J1 (RX1B_N), U4.J2 (VSSA), U4.K1 (RX1C_P), U4.K2 (VSSA), U4.K12 (VSSD), U4.L1 (RX1C_N), U4.L2 (VSSA), U4.L3 (VSSA), U4.L7 (VSSA), U4.L8 (VSSA), U4.L9 (VSSA), U4.L10 (VSSA), U4.L11 (VSSA), U4.L12 (VSSA), U4.M3 (NC), U4.M4 (VSSA), U4.M5 (TX_MON), U4.M6 (VSSA), U11.2 (GND_2), Y6.1 (GROUND_1), Y6.2 (GROUND_2); also elsewhere on the board
unnamed: C91.1, R31.2
unnamed: C97.1, R32.2
unnamed: C120.2, T6.6
unnamed: C121.2, T6.4
unnamed: C317.2, T4.6
unnamed: C318.2, T4.4
unnamed: D5.2, J14.1, T6.3
unnamed: D12.2, J12.1, L11.2, U11.3
unnamed: C95.1, IC2.1 (SIGNAL), R33.1
unnamed: C312.1, C313.1, IC14.5 (VOUT), Y6.4 (VDD)
unnamed: T4.3, U11.1
unnamed: R32.1, U4.G2 (RX_VCO_LDO_OUT), U4.G3 (VDDA1P1_RX_VCO)
unnamed: R31.1, U4.A11 (VDDA1P1_TX_VCO), U4.B11 (TX_VCO_LDO_OUT)
unnamed: C119.2, TP5.1 (1_1), U4.B3 (AUXDAC1)
unnamed: R34.2, U4.L4 (RBIAS)
unnamed: C95.2, U4.M12 (XTALN), Y6.3 (OUTPUT)

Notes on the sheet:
FPGA INTEFACE(LVDS_25)
TRANSMITTER
[2]
RECIEVER
MISC.
References:
[3]
[4]
POWER
DECOUPLING
[1]

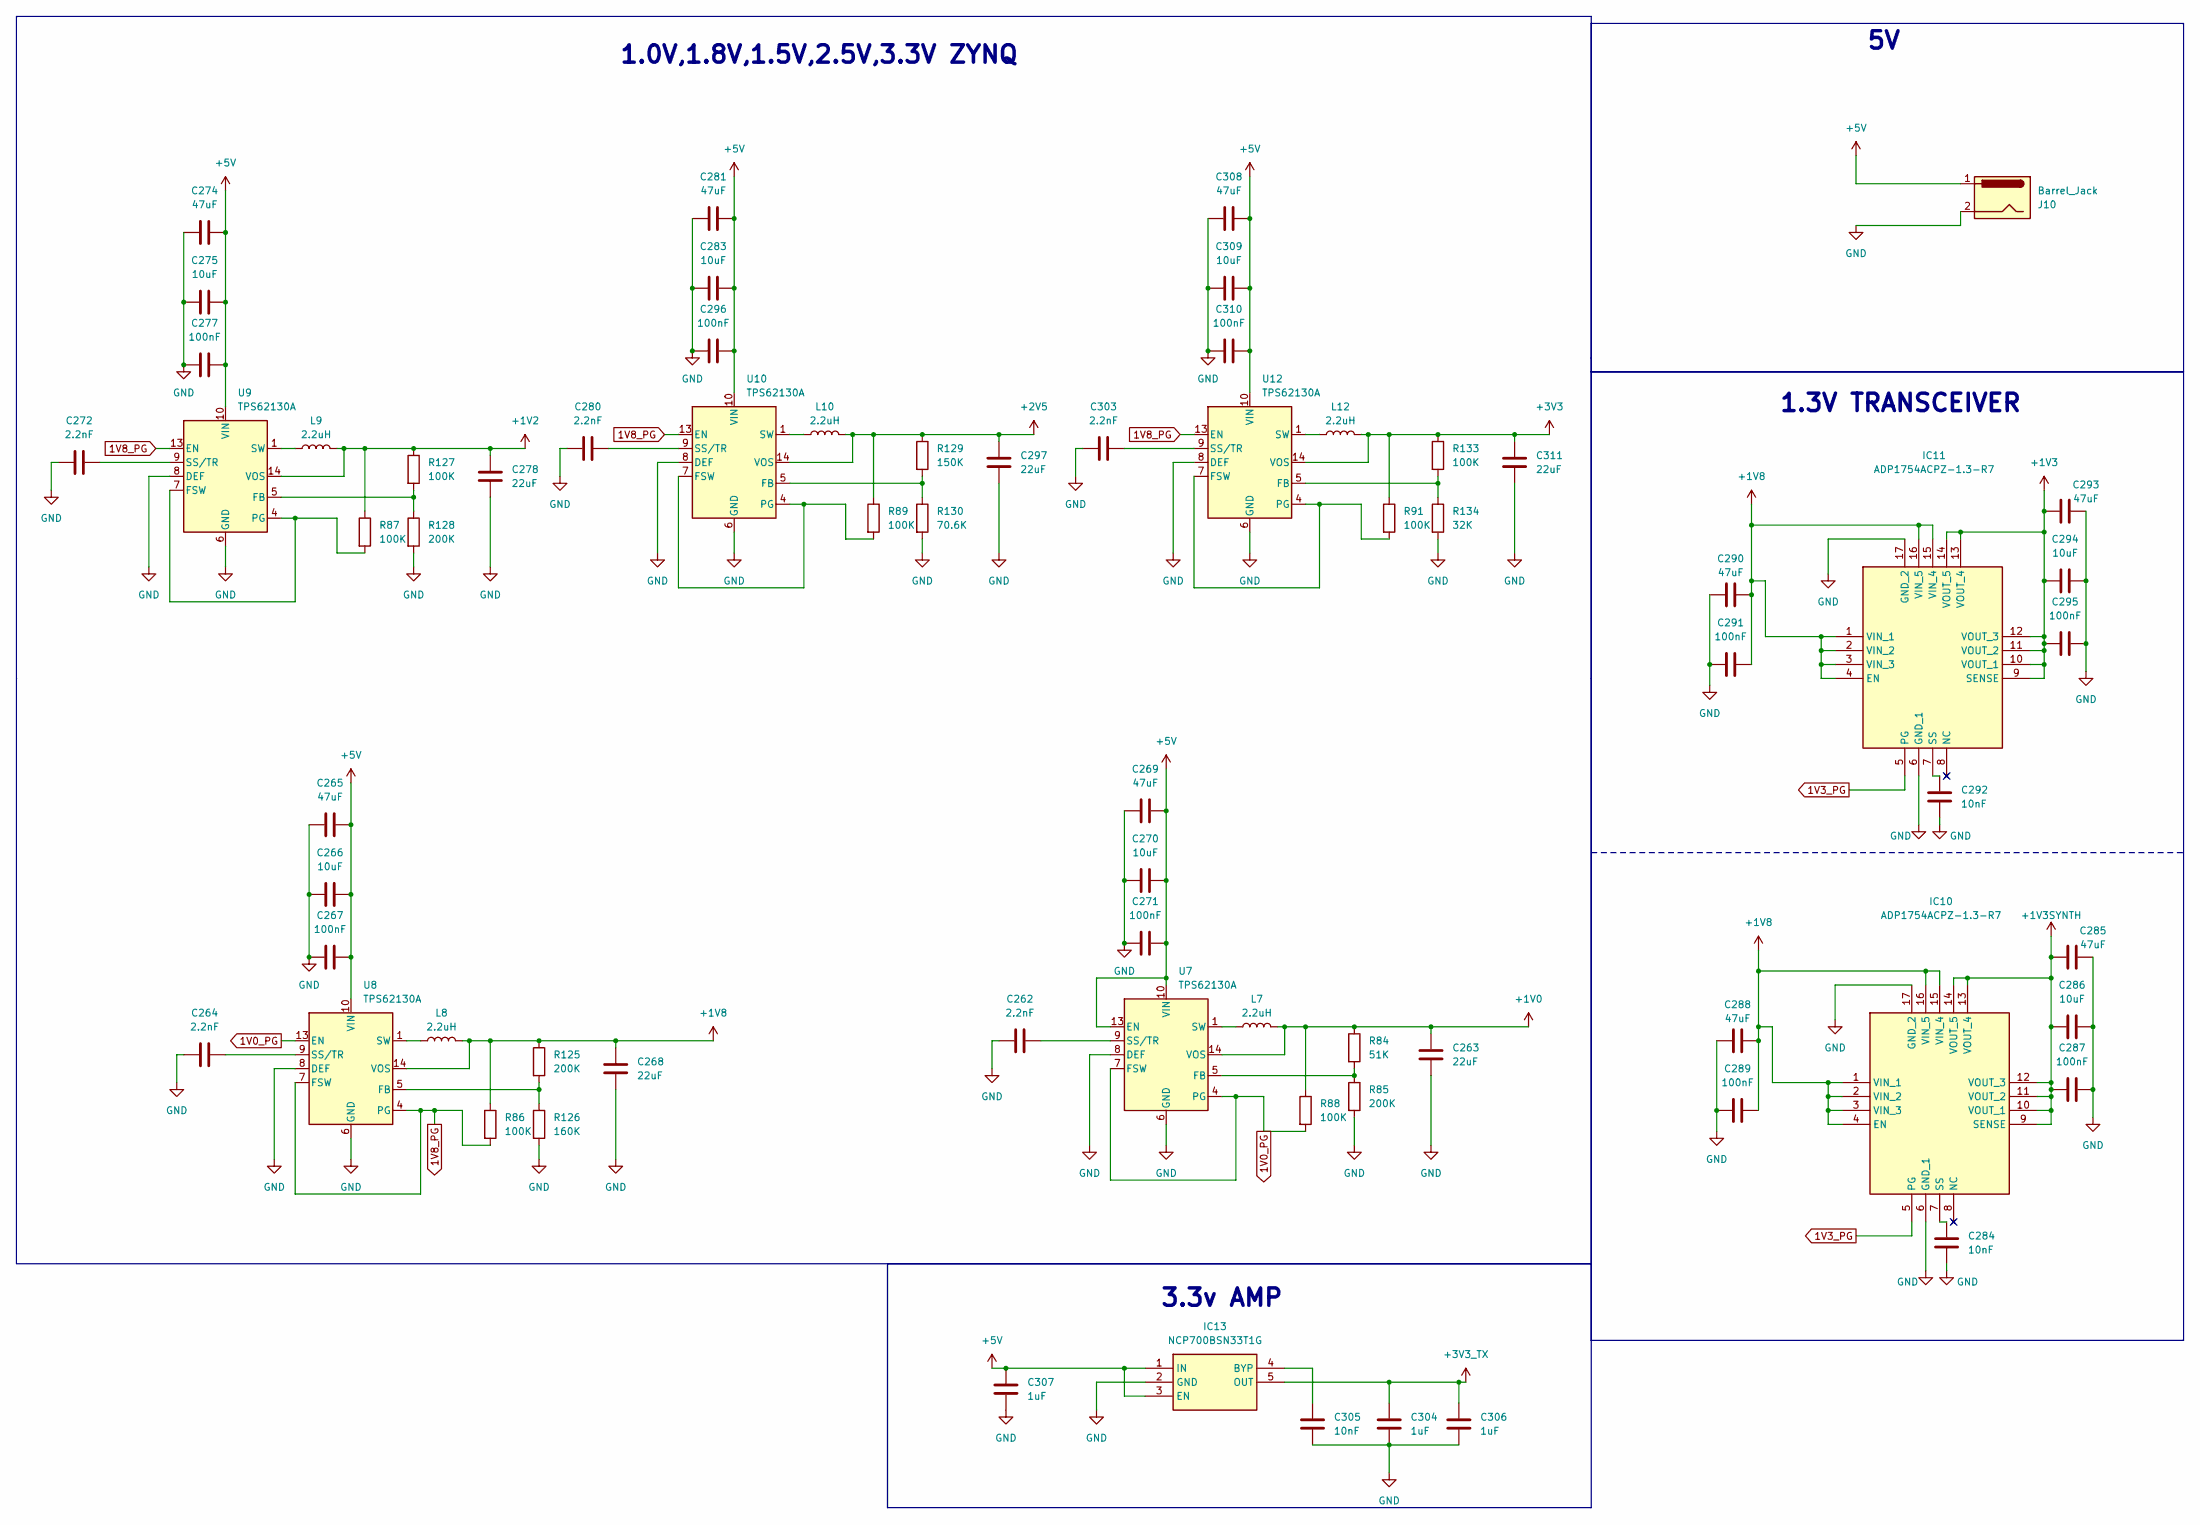
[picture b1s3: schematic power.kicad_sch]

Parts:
C262, C264, C272, C280, C303: 2.2nF; C_0201_0603Metric
C263, C268, C278, C297: 22uF; C_0603_1608Metric
C265, C269, C274, C281, C285, C288, C290, C293, C308: 47uF; C_0603_1608Metric
C266, C270, C275, C283, C286, C294, C309: 10uF; C_0603_1608Metric
C267, C271, C277, C287, C289, C291, C295, C296, C310: 100nF; C_0402_1005Metric
C284, C292, C305: 10nF; C_0201_0603Metric
C304, C306, C307: 1uF; C_0402_1005Metric
C311: 22uF; C_0805_2012Metric
IC10, IC11: ADP1754ACPZ-1.3-R7; QFN65P400X400X80-17N-D; Manufacturer_Part_Number ADP1754ACPZ-1.3-R7; Mouser Part Number 584-P1754ACPZ13R7
IC13: NCP700BSN33T1G; SOT95P275X110-5N; Manufacturer_Part_Number NCP700BSN33T1G; Mouser Part Number 863-NCP700BSN33T1G
J10: Barrel_Jack; BarrelJack_CUI_PJ-063AH_Horizontal
L7, L8, L9, L10, L12: 2.2uH; XFL4020-222ME
R84: 51K; R_0402_1005Metric
R85, R125, R128: 200K; R_0402_1005Metric
R86, R87, R88, R89, R91, R127, R133: 100K; R_0402_1005Metric
R126: 160K; R_0402_1005Metric
R129: 150K; R_0402_1005Metric
R130: 70.6K; R_0402_1005Metric
R134: 32K; R_0402_1005Metric
U7, U8, U9, U10, U12: TPS62130A; VQFN-16-1EP_3x3mm_P0.5mm_EP1.68x1.68mm_ThermalVias

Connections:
1V0_PG: R88.2, U7.4 (PG), U7.7 (FSW), U8.13 (EN)
1V3_PG: IC10.5 (PG), IC11.5 (PG)
1V8_PG: R86.2, U8.4 (PG), U8.7 (FSW), U9.13 (EN), U10.13 (EN), U12.13 (EN)
+1V0: C263.1, L7.2, R84.1, R88.1, U7.14 (VOS); also elsewhere on the board
+1V2: C278.1, L9.2, R87.1, R127.1, U9.14 (VOS); also elsewhere on the board
+1V3: C293.1, C294.1, C295.1, IC11.9 (SENSE), IC11.10 (VOUT_1), IC11.11 (VOUT_2), IC11.12 (VOUT_3), IC11.13 (VOUT_4), IC11.14 (VOUT_5); also elsewhere on the board
+1V3SYNTH: C285.1, C286.1, C287.1, IC10.9 (SENSE), IC10.10 (VOUT_1), IC10.11 (VOUT_2), IC10.12 (VOUT_3), IC10.13 (VOUT_4), IC10.14 (VOUT_5); also elsewhere on the board
+1V8: C268.1, C288.2, C289.2, C290.2, C291.2, IC10.1 (VIN_1), IC10.2 (VIN_2), IC10.3 (VIN_3), IC10.4 (EN), IC10.15 (VIN_4), IC10.16 (VIN_5), IC11.1 (VIN_1), IC11.2 (VIN_2), IC11.3 (VIN_3), IC11.4 (EN), IC11.15 (VIN_4), IC11.16 (VIN_5), L8.2, R86.1, R125.1, U8.14 (VOS); also elsewhere on the board
+2V5: C297.1, L10.2, R89.1, R129.1, U10.14 (VOS); also elsewhere on the board
+3V3: C311.1, L12.2, R91.1, R133.1, U12.14 (VOS); also elsewhere on the board
+3V3_TX: C304.1, C306.1, IC13.5 (OUT); also elsewhere on the board
+5V: C265.2, C266.2, C267.2, C269.2, C270.2, C271.2, C274.2, C275.2, C277.2, C281.2, C283.2, C296.2, C307.1, C308.2, C309.2, C310.2, IC13.1 (IN), IC13.3 (EN), J10.1, U7.10 (VIN), U7.11 (VIN), U7.12 (VIN), U7.13 (EN), U8.10 (VIN), U8.11 (VIN), U8.12 (VIN), U9.10 (VIN), U9.11 (VIN), U9.12 (VIN), U10.10 (VIN), U10.11 (VIN), U10.12 (VIN), U12.10 (VIN), U12.11 (VIN), U12.12 (VIN); also elsewhere on the board
GND: C262.1, C263.2, C264.1, C265.1, C266.1, C267.1, C268.2, C269.1, C270.1, C271.1, C272.1, C274.1, C275.1, C277.1, C278.2, C280.1, C281.1, C283.1, C284.1, C285.2, C286.2, C287.2, C288.1, C289.1, C290.1, C291.1, C292.1, C293.2, C294.2, C295.2, C296.1, C297.2, C303.1, C304.2, C305.2, C306.2, C307.2, C308.1, C309.1, C310.1, C311.2, IC10.6 (GND_1), IC10.17 (GND_2), IC11.6 (GND_1), IC11.17 (GND_2), IC13.2 (GND), J10.2, R85.2, R126.2, R128.2, R130.2, R134.2, U7.6 (GND), U7.8 (DEF), U7.15 (GND), U7.16 (GND), U7.17 (GND), U8.6 (GND), U8.8 (DEF), U8.15 (GND), U8.16 (GND), U8.17 (GND), U9.6 (GND), U9.8 (DEF), U9.15 (GND), U9.16 (GND), U9.17 (GND), U10.6 (GND), U10.8 (DEF), U10.15 (GND), U10.16 (GND), U10.17 (GND), U12.6 (GND), U12.8 (DEF), U12.15 (GND), U12.16 (GND), U12.17 (GND); also elsewhere on the board
unnamed: C284.2, IC10.7 (SS)
unnamed: C292.2, IC11.7 (SS)
unnamed: C305.1, IC13.4 (BYP)
unnamed: L7.1, U7.1 (SW), U7.2 (SW), U7.3 (SW)
unnamed: L8.1, U8.1 (SW), U8.2 (SW), U8.3 (SW)
unnamed: L9.1, U9.1 (SW), U9.2 (SW), U9.3 (SW)
unnamed: L10.1, U10.1 (SW), U10.2 (SW), U10.3 (SW)
unnamed: L12.1, U12.1 (SW), U12.2 (SW), U12.3 (SW)
unnamed: R84.2, R85.1, U7.5 (FB)
unnamed: C262.2, U7.9 (SS/TR)
unnamed: R125.2, R126.1, U8.5 (FB)
unnamed: C264.2, U8.9 (SS/TR)
unnamed: R127.2, R128.1, U9.5 (FB)
unnamed: R87.2, U9.4 (PG), U9.7 (FSW)
unnamed: C272.2, U9.9 (SS/TR)
unnamed: R129.2, R130.1, U10.5 (FB)
unnamed: R89.2, U10.4 (PG), U10.7 (FSW)
unnamed: C280.2, U10.9 (SS/TR)
unnamed: R133.2, R134.1, U12.5 (FB)
unnamed: R91.2, U12.4 (PG), U12.7 (FSW)
unnamed: C303.2, U12.9 (SS/TR)

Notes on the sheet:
3.3v AMP
1.0V,1.8V,1.5V,2.5V,3.3V ZYNQ
1.3V TRANSCEIVER
